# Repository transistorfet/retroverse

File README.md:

RetroVerse
==========

###### *Started August 06, 2023*

A collection of computer cards using the [VME bus](https://en.wikipedia.org/wiki/VMEbus) as a common
backplane, in the style of modular computer equipment, laboratory test equipment, and industrial
controls systems.  The project name is a combination of Retro-computers (newly designed and built
computers that are based on old CPUs and parts), and Versa (the V in VME, which stands for Versa
Module Eurocard).

I've always liked the VME bus for its adaptability.  It's an asynchronous bus with dynamic sizing,
so it can support both controllers and peripherals that require different signaling speeds and bus
widths to communicate, without requiring a specialized bus interface chip.  It supports multiple
controllers without the need for a special slot on the backplane, because it uses daisy chained
priority bus arbitration.  It's based on the Eurocard standard form factor, and uses standard and
readily available DIN41612 connectors, comes in a 3U variant, and it's possible to still buy
equipment that conforms to the standard, namely card cases and power supplies.  The 3U Eurocard
standard, which uses 160x100mm boards, is also fairly affordable for PCB printing, and it's possible
to make not-quite-standard 100x100mm cards, which can be printed for as low as $2.  The bus is
perhaps slow by modern standards, but for CPUs that are below 100MHz, it's the perfect bus to build
16-bit and 32-bit retro computers around.

So far, I have bought an off-the-shelf desktop card case from
[Schroff](https://schroff.nvent.com/en-de/products/enc24576-106) via Digikey (backordered), a used
Schroff 3U 11-slot backplane from eBay, and an affordable [MeanWell power
supply](https://www.meanwell.com/productPdf.aspx?i=488) to power it.  I've designed and built a CPU
card with a Motorola MC68030, onboard static RAM and Flash memory, and two serial ports, a small
16-bit memory card with up to 4MB of static RAM, and a board for handling the bus arbitration and
interrupt signals on the bus (separate from the CPU card since I intend to use multiple CPU cards in
the same system).  I've also built Tom Storey's CompactFlash card from
[COMET](https://github.com/tomstorey/COMET) to use as the main secondary storage for the system.
Before building these, I had also designed and built a generic card using an STM32 microcontroller
wired to the bus signals called
[BigBoy](https://github.com/transistorfet/retroverse/tree/main/components/bigboy), which I had hoped
to use as a bus analyzer, but it's a bit too slow for that, so I'll probably program it as a generic
peripheral instead.

I had originally intended to design and build my own backplane using 4-row connectors with some of
the P2 connector's signals on an extended P1, but I abandoned that idea in the interest of
interoperability with existing used VME equipment and ended up buying a used 11-slot Schroff
backplane from eBay.  Tom Storey has designed a 3-slot and 8-slot backplane as part of
[COMET](https://github.com/tomstorey/COMET) which is a good choice for those who wish to build their
own.

I also intend to eventually make an MC68010 version using only DIP chips and hopefully all hardwired
logic, so that there's no need for specialized PLD programmers.  I might also make cards with other
CPUs.  It should be possible for the system to support different CPUs in the same system at the same
time, running their own code.  My larger hope is for the VME bus to be used more broadly in the
hobbyist retro computer community as a common means of constructing systems.

Some of the design and build process was live-streamed and recordings are available at
[youtube.com/@transistorfet](https://www.youtube.com/@transistorfet)

Why VMEbus?
-----------

* it uses the eurocard form factor, and equipment such as cases can still be bought new or used

* it's asynchronous, so it can support devices operating at different speeds

* it supports dynamic bus sizing for 8-bit, 16-bit, and multiplexed 32-bit operations in 3U

* in the 6U form factor, it can also support full 32-bit or multiplexed 64-bit operations

* the DIN41612 connectors it uses are still widely available with solder tails

* supports cheap 3U board sizes of 100mm x 160mm or 100mm x 100mm

* also supports 6U board sizes for bigger and more complex devices

Why Not VMEBus?
---------------

* it can be a bit more complicated to interface to for simple 8-bit systems

* it's slower than newer buses like CompactPCI

* when using passive termination instead of active termination, it can draw a lot of current (2A+)
  with no cards

* each signal can draw a fair amount of current, which may be out of range for some logic chips (the
  standard requires that each pin can sink 48mA or more but typically it's <25mA in smaller and
  slower systems)

About VMEbus
------------

* [Understanding VMEBus](https://mdavidsaver.github.io/epics-doc/vme/understanding-vme.pdf)
* [VME FAQ from VITA](https://www.vita.com/VMEbus-FAQ)
* [VME P1 Connector Pinout](https://allpinouts.org/pinouts/connectors/buses/vme-versamodule-eurocard-p1/)
* [VME64](https://www.ge.infn.it/~musico/Vme/Vme64.pdf)
* [VMEBus on InterfaceBus.com](https://web.archive.org/web/20231220065144/http://www.interfacebus.com/Design_Connector_VME.html)

Other VME Projects
------------------

#### VMEbus prototyping card PCB:

* [https://github.com/rhaamo/VME](https://github.com/rhaamo/VME)

#### Proto Boards, Blanking Plates, Plate Adapters, ECB backplanes:

* [https://www.ebay.ca/usr/martenelectric](https://www.ebay.ca/usr/martenelectric)
* [https://www.martenelectric.cz/index.html](https://www.martenelectric.cz/index.html)

#### COMET backplane, prototyping card, and single board computer:

* [https://hackaday.io/project/192539-comet68k](https://hackaday.io/project/192539-comet68k)
* [https://github.com/tomstorey/COMET](https://github.com/tomstorey/COMET)
* computer card is missing bus arbitration, but the backplane supports it

[If you know of any other hobbyist VME components or projects that others can build, please get in
contact with me.  I'd love to add them to this list]

Single-CPU System
-----------------

This is generally where I'm at, as of March 2025.  I have a simple single-CPU system with
SystemBoard, k30p-VME, Tom Storey's CF Card, and MemBird Woodcock (although it's not used by the
software atm).  It can boot [Gloworm](https://github.com/transistorfet/gloworm), using the CF card
as the ATA device, and the FTDIs on k30p as the TTY and a SLIP connection for networking.  I can
ping it from my computer over SLIP, and run applications off the CF card.

![alt text](images/complete-single-cpu-system-front.jpg "A schroff 3U 63HP PropacPro case, looking face on and a bit downward at the front, which is trimmed in a very dark grey aluminum piece with two straight dull blue rounded aluminum top and bottom trim above and below where the cards are inserted.  The top of the case, which is barely showing, is light grey.  It has space for 15 slots spaced out horizontally, where cards can be inserted, oriented vertically, along bright red plastic guide rails.  Only 7 of the 10 guide rails are showing, with the others blocked by the front panels of 3 of the cards, with a gap of 3 slots between the second and third one.  The right 5 slots don't have guide rails.  The left-most slot has a blank aluminum plate with a few holes in it that allow a bright deep green LED inside to shine through.  Next to it is a white aluminum panel with black text that shows a partially obscured ComputieVME with a Motorola logo and k30p-VME below that.  It has 4 rows of pairs of LEDs and buttons, two USB-C ports with a mauve and a teal green cable plugged into each, and a white trapezoid handle below.  There's an empty slot and then Tom Storey's CF card is next to that with a CompactFlash card inserted in the front and no front panel.  Membird is next to it but not visible except for the dull green power LED.  BigBoy with a similar custom white aluminum front panel is next to it, with BigBoy in black text, 2 x 2 blue LEDs, a microSD slot, microB USB and RJ-11 jack labelled Ethernet on the front panel.  The right half of the 11-slot VME backplane is just visible, mounted in the left part of the case, with a space visible in the back where the remaining 4-slots-worth of space shows the back of the case, and the rear of the black power entry module.  Mounted in the right-most side of the case is a Meanwell powersupply taking up 8HP (2 slots), and the full 3U of height, wrapped in a thin metal shell with a diagonal pattern of round holes that expose most of the inside.  An 8HP blank plate with 4 knurled thumb-screws in the 4 corners and a trapezoid handle at the bottom and a protective film with 2 vertical blue lines still covering it, is mounted in the right most spot to block the power supply.")
![alt text](images/basic-single-cpu-system-angle.jpg "A green PCB backplane that says Schroff with white DIN41612 connectors, and 4 cards plugged into the first 4 of 11 slots.  The first and last are short 100mm long cards with the last being red and shown clearly while the first is black and is mostly obscured by the others.  The second card is purple with a white aluminum frontpanel that says 'ComputieVME', a Motorola logo, and 'k30p-VME' near the top in black text, with a trapezoid grey handle at the bottom, and two USB-C cables coming out of the frontpanel, the top one being a mauve and the the bottom being a light teal green.  The third card is green and has a compact flash card sticking out the top with no frontpanel.  The view is looking mostly down and to the left with the backplane flat on a black metal shelving unit about waist high, with the cards sticking upwards.  An oscilloscope can be be seen on the same shelf behind the backplane, and a small white fan is just out of view.")
![alt text](images/basic-single-cpu-system-side-angle.jpg "A green PCB backplane with white DIN41612 connectors, and 4 cards plugged into the first 4 of 11 slots.  The first and last are short 100mm long cards with the last being red and can mostly been seen while the first is black and is mostly obscured by the others.  The second card is purple with a white aluminum frontpanel with a trapezoid grey handle at the bottom, and two USB-C cables coming out of the frontpanel, the top one being a mauve and the the bottom being a light teal green.  The third card is green and has a compact flash card sticking out the top with no frontpanel.  The view is looking mostly sideways and a bit to the left, with backplane flat on a black metal shelving unit about waist high, with the cards sticking upwards.  An oscilloscope can be be seen on the same shelf behind the backplane, partially obscured by the cards.  A small white fan is just out of view, and a small teal desk lamp is in the foreground shining on the cards.")

Desktop Case
------------

I bought a brand new Schroff PropacPro 3U 63HP 266mm deep Unshielded Complete Desktop case.  I
initially requested a quote from Schroff, but unsurprisingly they sent me back a list of authorized
redistributors instead.  It turned out that Digikey did actually have the cases available for
backorder but the listing was uncategorized, so you had to search specifically for the part number
to find it.

* [https://schroff.nvent.com/en-ca/products/enc24576-006](https://schroff.nvent.com/en-ca/products/enc24576-006)
* [https://www.digikey.ca/en/products/detail/schroff/24576006/24659562](https://www.digikey.ca/en/products/detail/schroff/24576006/24659562)

I also bought a [Schurter Power Entry
Module](https://www.digikey.ca/en/products/detail/schurter-inc/4304-6091/2645678) and cut a hole in
the back aluminum panel to install it.  It's wired to the Meanwell RT-85B power supply, and power
from that is wired to the backplane.  I'd like to eventually add a current meter on the front,
mounted in an 8HP blanking plate I've bought, but I'm still waiting for parts to arrive.

![alt text](images/Schroff-case-and-backplane.jpg "A 3U 63HP desktop case with very dark grey front front and dull blue trim pieces made of rounded aluminum above and below the front card mounting rails, which have many small M2.5 screw holes horizontally, top and bottom, and are bright bare aluminum.  The left most 10-slots out of a maximum 15 have bright red card guides.  The case is empty of cards, but a Schroff 11-slot backplane is mounted in the rear of the case, most of the way back, and the rear panel is not in place.  The backplane is a green PCB with large white DIN41612 connectors that take up as much space as there is exposed green PCB.  The rest of the inside of the case is untreated bare aluminum.  A bundle of blue covered wire pair is just visible behind the case to the left, and a desk lamp and lego flowers are way in the background to the left, and a trans flag is barely visible to the right.")
![alt text](images/Schroff-case-and-backplane-rear.jpg "The rear of a 3U 63HP desktop case with no back panel looking inward, with a big green PCB with yellow silkscreen and yellow vertical through-hole resistor networks on the left and right sides, a white pin connector on the right most side, orange capacitors and metal screw terminals for power along the bottom edge, and the pins of the back sides of the DIN41612 sockets showing through.  It is covering most of the right side of the inside of the case, mounted on the rear rails inside the case.  The case is a light grey aluminum with vertical plastic rear feet/bumpers on the left and right sides.")
![alt text](images/Schroff-case-rear-panel-with-custom-switch.jpg "The rear of a 3U 63HP desktop case with no back panel looking inward, with a big green PCB with yellow silkscreen and yellow vertical through-hole resistor networks on the left and right sides, a white pin connector on the right most side, orange capacitors and metal screw terminals for power along the bottom edge, and the pins of the back sides of the DIN41612 sockets showing through.  It is covering most of the right side of the inside of the case, mounted on the rear rails inside the case.  The case is a light grey aluminum with vertical plastic rear feet/bumpers on the left and right sides.")

Backplane
---------

I bought a Schroff 23000-041 11-Slot backplane, used from eBay.  Luckily it has automatic
daisy-chaining, so when a slot doesn't have a card in it, the daisy-chained signals are shorted in
order to bypass that slot.  It also has active termination, which I have enabled with the jumpers,
so it takes only 10mA of 5V power without any cards connected.

k30p-VME
--------

A CPU card with a Motorola 68030 CPU, and an ATF1508AS CPLD for the control logic.  It has 2MB of
static RAM onboard, 512KB of Flash, a MC68681 dual serial port controller, with space for two
onboard FTDIs, and some push-button and LEDs that can be controlled by the serial controller.  The
CPLD can control the onboard transceivers to make a VME request from the CPU, based on the address
that the CPU is requesting.  I've tested it with 8-bit and 16-bit cycles, but I've designed it with
the transceivers that are required to make an A40/MD32 bus access, and hope to implement it soon
using BigBoy as the test peripheral.

While building the first revision, I found a number of issues.  The transceivers don't turn off when
the CPLD is being programmed, or when it's unprogrammed, and that means they write into each other,
and can damage each other.  I reworked in some pull-up resistors for the /OE signals to disable the
transceivers when the CPLD outputs are low or tri-stated.  I also originally had the FTDI powered by
the board, which meant it would disconnect from the computer every time the board was power cycled,
which was quite problematic when testing.  I tried to rework it so that it was powered by the USB
bus, but at first that didn't work.  After replacing the chip with an external FTDI, I tried
reworking it again and found that the USB-C cable only works in one orientation because I don't have
the main differential pair from each side of the USB-C connector jumped together.  The full errata
is here:
[k30p-VME-rev1-errata](https://github.com/transistorfet/retroverse/blob/main/components/computie-vme/hardware/k30p-VME/revisions/k30p-VME-rev1-errata.txt)

![alt text](images/k30p-VME-rev.1-reworked-assembled.jpg "The fully assembled and unplugged k30p-VME CPU Card, with purple solder mask, white silkscreen text, and a big greyish-white DIN41612 connector on the right side.  A big black plastic PGA chip in the centre reads MC68030RP33B.  There is some rework to the transceivers on the right, with some chip resistors and red 30AWG wire soldered in place, and some red 30AWG wire around the FTDIs on the left to power them from the USB bus.  A mauve-coloured USB-C cable is connected to the first USB port and a teal green USB-C cable is connected to the second USB port (bottom)")

, a fuse holder, and a plug for an IEC power cable.  It's laying flat on the desk and just in view is the rear section of the inside frame of the case with the top and bottom panels removed showing the shiny aluminum rails with black silkscreen text showing the number markings from 1 to 63 HP, two rows which count in opposite directions and can be read in the orientation of ascending numbers (ie. the bottom row is right way up and the top row is upside down but could be read the right way from 1-63 if if the rail was turned around)")

MemBird Woodcock
----------------

A memory card with up to 4MB of either Static RAM or Pseudo-static RAM powered by either 5V or 3.3V,
which can be selected by a soldered jumper and by using different chips (memory and transceiver
chips in particular).  It can only respond to A24 cycles, and only 8-bit or 16-bit accesses, but
that should serve well enough as common memory for when I have multiple CPU cards.  In future I will
make another MemBird board with an FPGA and SDRAM to allow for 128MB+ of memory, but until then,
this will suffice.

The building of this board went really smoothly.  Soldering went better than normal for SMT parts.
I was using ChipQuik NoClean Liquid flux, which worked well.  I only had one chip that was visibly
unconnected on closer inspection, and I didn't find any unintended bridges.  The board was behaving
strangely when I first tested it before I cleaned the flux off, but once I cleaned it and let it dry
overnight, it worked perfectly.

It's named after the American Woodcock, a small bird that moves along with a slow rhythmic walk,
since this card only has a small amount of memory, and will be slower to access, being only 16-bits.

SystemboardSMT
--------------

A system board with an ATF1508AS in the centre, and a clock, and that's about it.  It's primary
function is to handle the bus arbitration logic, but I can also use it as a dummy 8-bit peripheral
for testing.

I designed and built this board second, before the k30p and MemBird Woodcock, because it was simple
and would act as a test for the ATF1508, which I hadn't used before (other than in the devkit I
bought from Atmel).  The initial logic for the bus arbitration state machine turned out to be very
wrong, and that was causing problems for the k30p, which was hanging indefinitely.  I thought it was
the k30p's logic, but it turned out it wasn't receiving the bus grant from this card.

BigBoy
------

This was the first card I made and I intended to use it as a bus analyzer among other things, but
it's a bit too slow to catch most cycles, so I think I'll need an FPGA card instead for that
function, but it can work as a slow peripheral.  It has an STM32H743 microcontroller in a 208 pin
QFP package in the centre with the 5V tolerant I/O connected directly to the VME bus for the control
signals, and through transceivers for the data and address signals.  On the board is also a 100BaseT
ethernet interface, a full speed USB port (so 12Mbps I assume is the fastest), a microSD card slot
(where I accidentally put the footprint on backwards), and a few headers for external FTDIs, I2C,
and SPI devices.

It's called BigBoy because it has the big boy microcontroller in the largest QFP package available,
with a big 4-row DIN41612 connector which was an idea to add an extra row to P1 for the upper data
and address signals of a 32-bit system, which is optional (the 4-row connector can be plugged into a
3-row or 4-row backplane).  I've mostly abandoned this idea in favour of sticking to the standard,
and using the A40/MD32 cycle on a 3U system, or perhaps eventually making a 6U system and cards if I
want full-sized, higher speed, 32- or 64-bit systems in the future, all while maintaining
interoperability with existing used backplanes.  The logo is of [Bronson the
Cat](https://www.instagram.com/iambronsoncat/?hl=en) who is *such a big boy*

. It has a large grep DIN41612 connector on the right side, and a metal-shielded RJ-45 jack and some buttons and LEDs on the left.")

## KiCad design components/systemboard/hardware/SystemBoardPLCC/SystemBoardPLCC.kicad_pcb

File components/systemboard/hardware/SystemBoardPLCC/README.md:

SystemBoard
===========

Status: Never Built

Latest: Rev. 1

### About

A somewhat generic card with an ATF1508 programmable logic device, which is intended to act as the
system board of the VME bus, handling the resolution and granting of the bus during bus
arbitration, and interrupt acknowledging.  It has a clock and a reset button, which can be
programmed in the logic to reset all devices on the bus.

I have not actually built this version of the card, and instead built the SystemBoardSMT after
finding out that the PLCC version of the ATF1508AS was End-of-Life, and out of stock at Digikey
and Mouser.  It should work, but I'd recommend comparing the signals to the other version.  There
maybe be one or two signals that should be shuffled, depending on what's most important.

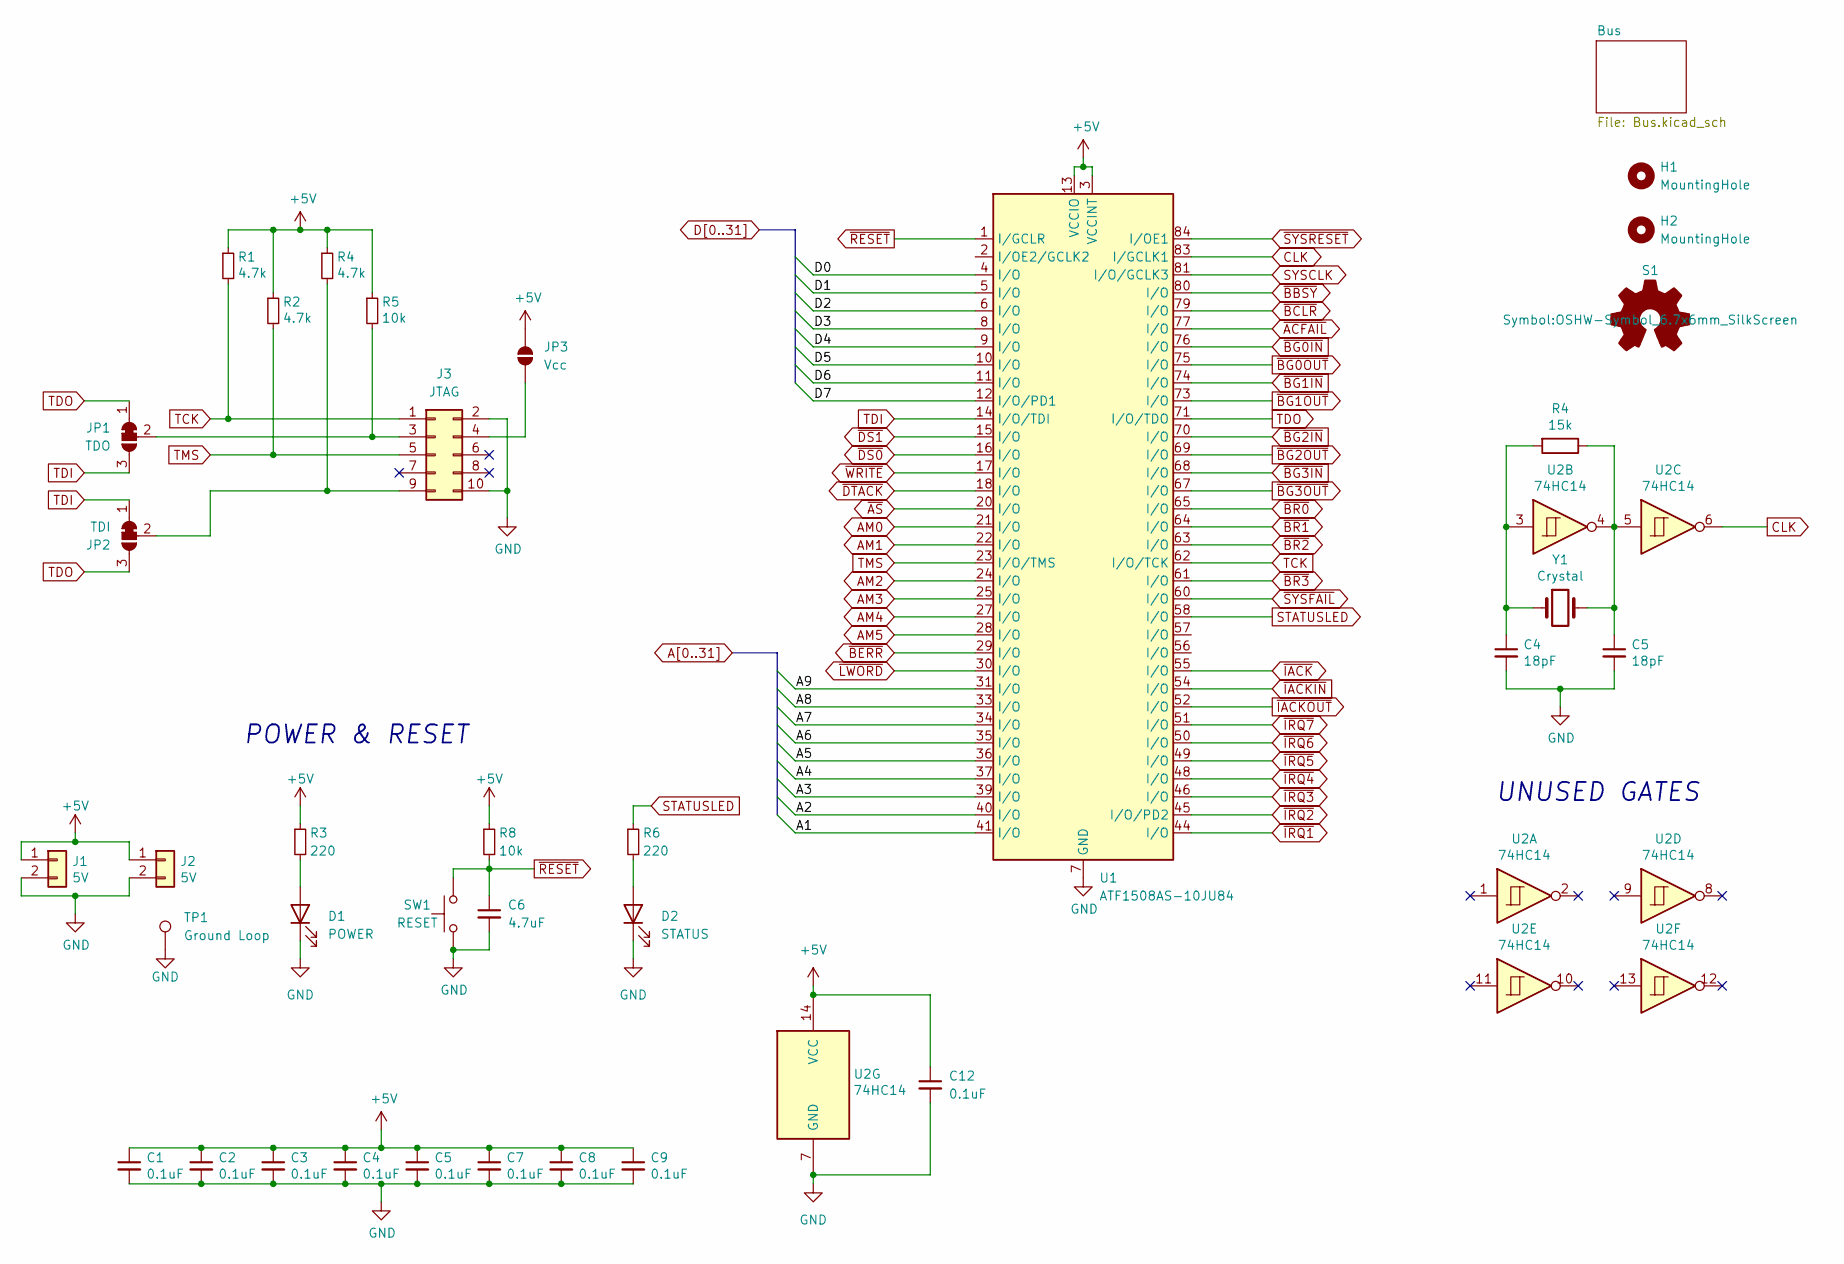
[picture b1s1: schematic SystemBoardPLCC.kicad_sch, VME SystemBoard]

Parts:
C1, C2, C3, C4, C7, C8, C9, C12: 0.1uF; C_0805_2012Metric_Pad1.18x1.45mm_HandSolder
C5: 18pF; C_Disc_D3.0mm_W2.0mm_P2.50mm
C6: 4.7uF; C_0805_2012Metric_Pad1.18x1.45mm_HandSolder
D1: POWER; LED_D3.0mm
D2: STATUS; LED_D3.0mm
H1, H2: MountingHole; MountingHole_2.7mm_M2.5_DIN965
J1, J2: 5V; PinHeader_1x02_P2.54mm_Vertical
J3: JTAG; PinHeader_2x05_P2.54mm_Vertical
JP1: TDO; SolderJumper-3_P1.3mm_Bridged12_RoundedPad1.0x1.5mm_NumberL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
JP2: TDI; SolderJumper-3_P1.3mm_Bridged12_RoundedPad1.0x1.5mm_NumberL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
JP3: Vcc; SolderJumper-2_P1.3mm_Open_RoundedPad1.0x1.5mm
R1, R2, R4: 4.7k; R_Axial_DIN0204_L3.6mm_D1.6mm_P5.08mm_Horizontal
R3, R6: 220; R_Axial_DIN0204_L3.6mm_D1.6mm_P5.08mm_Horizontal
R5, R8: 10k; R_Axial_DIN0204_L3.6mm_D1.6mm_P5.08mm_Horizontal
S1: Logo_Open_Hardware_Small; OSHW-Symbol_6.7x6mm_SilkScreen
SW1: RESET; SW_PUSH_6mm
TP1: Ground Loop; TestPoint_Loop_D2.60mm_Drill1.6mm_Beaded
U1: ATF1508AS-10JU84; PLCC-84_THT-Socket
U2: 74HC14; DIP-14_W7.62mm_LongPads
Y1: Crystal; Crystal_HC49-4H_Vertical

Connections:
A1: U1.41 (I/O); also elsewhere on the board
A2: U1.40 (I/O); also elsewhere on the board
A3: U1.39 (I/O); also elsewhere on the board
A4: U1.37 (I/O); also elsewhere on the board
A5: U1.36 (I/O); also elsewhere on the board
A6: U1.35 (I/O); also elsewhere on the board
A7: U1.34 (I/O); also elsewhere on the board
A8: U1.33 (I/O); also elsewhere on the board
A9: U1.31 (I/O); also elsewhere on the board
AM0: U1.21 (I/O); also elsewhere on the board
AM1: U1.22 (I/O); also elsewhere on the board
AM2: U1.24 (I/O); also elsewhere on the board
AM3: U1.25 (I/O); also elsewhere on the board
AM4: U1.27 (I/O); also elsewhere on the board
AM5: U1.28 (I/O); also elsewhere on the board
CLK: U1.83 (I/GCLK1), U2.6
D0: U1.4 (I/O); also elsewhere on the board
D1: U1.5 (I/O); also elsewhere on the board
D2: U1.6 (I/O); also elsewhere on the board
D3: U1.8 (I/O); also elsewhere on the board
D4: U1.9 (I/O); also elsewhere on the board
D5: U1.10 (I/O); also elsewhere on the board
D6: U1.11 (I/O); also elsewhere on the board
D7: U1.12 (I/O/PD1); also elsewhere on the board
GND: C1.2, C2.2, C3.2, C4.2, C5.2, C6.2, C7.2, C8.2, C9.2, C12.2, D1.1 (K), D2.1 (K), J1.2, J2.2, J3.2, J3.10, SW1.1, TP1.1, U1.7 (GND), U1.19 (GND), U1.32 (GND), U1.42 (GND), U1.47 (GND), U1.59 (GND), U1.72 (GND), U1.82 (GND), U2.7 (GND); also elsewhere on the board
unnamed: D1.2 (A), R3.2
unnamed: D2.2 (A), R6.2
unnamed: J3.3, JP1.2 (C), R5.2
unnamed: J3.4, JP3.1 (A)
STATUSLED: R6.1, U1.58 (I/O)
SYSCLK: U1.81 (I/O/GCLK3); also elsewhere on the board
TCK: J3.1, R1.2, U1.62 (I/O/TCK)
TDI: JP1.3 (B), JP2.1 (A), U1.14 (I/O/TDI)
TDO: JP1.1 (A), JP2.3 (B), U1.71 (I/O/TDO)
TMS: J3.5, R2.2, U1.23 (I/O/TMS)
~ACFAIL: U1.77 (I/O); also elsewhere on the board
~AS: U1.20 (I/O); also elsewhere on the board
~BBSY: U1.80 (I/O); also elsewhere on the board
~BCLR: U1.79 (I/O); also elsewhere on the board
~BERR: U1.29 (I/O); also elsewhere on the board
~BG0IN: U1.76 (I/O); also elsewhere on the board
~BG0OUT: U1.75 (I/O); also elsewhere on the board
~BG1IN: U1.74 (I/O); also elsewhere on the board
~BG1OUT: U1.73 (I/O); also elsewhere on the board
~BG2IN: U1.70 (I/O); also elsewhere on the board
~BG2OUT: U1.69 (I/O); also elsewhere on the board
~BG3IN: U1.68 (I/O); also elsewhere on the board
~BG3OUT: U1.67 (I/O); also elsewhere on the board
~BR0: U1.65 (I/O); also elsewhere on the board
~BR1: U1.64 (I/O); also elsewhere on the board
~BR2: U1.63 (I/O); also elsewhere on the board
~BR3: U1.61 (I/O); also elsewhere on the board
~DS0: U1.16 (I/O); also elsewhere on the board
~DS1: U1.15 (I/O); also elsewhere on the board
~DTACK: U1.18 (I/O); also elsewhere on the board
~IACKIN: U1.54 (I/O); also elsewhere on the board
~IACKOUT: U1.52 (I/O); also elsewhere on the board
~IACK: U1.55 (I/O); also elsewhere on the board
~IRQ1: U1.44 (I/O); also elsewhere on the board
~IRQ2: U1.45 (I/O/PD2); also elsewhere on the board
~IRQ3: U1.46 (I/O); also elsewhere on the board
~IRQ4: U1.48 (I/O); also elsewhere on the board
~IRQ5: U1.49 (I/O); also elsewhere on the board
~IRQ6: U1.50 (I/O); also elsewhere on the board
~IRQ7: U1.51 (I/O); also elsewhere on the board
~LWORD: U1.30 (I/O); also elsewhere on the board
~RESET: C6.1, R8.2, SW1.2, U1.1 (I/GCLR)
~SYSFAIL: U1.60 (I/O); also elsewhere on the board
~SYSRESET: U1.84 (I/OE1); also elsewhere on the board
~WRITE: U1.17 (I/O); also elsewhere on the board

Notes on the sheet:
POWER & RESET
UNUSED GATES

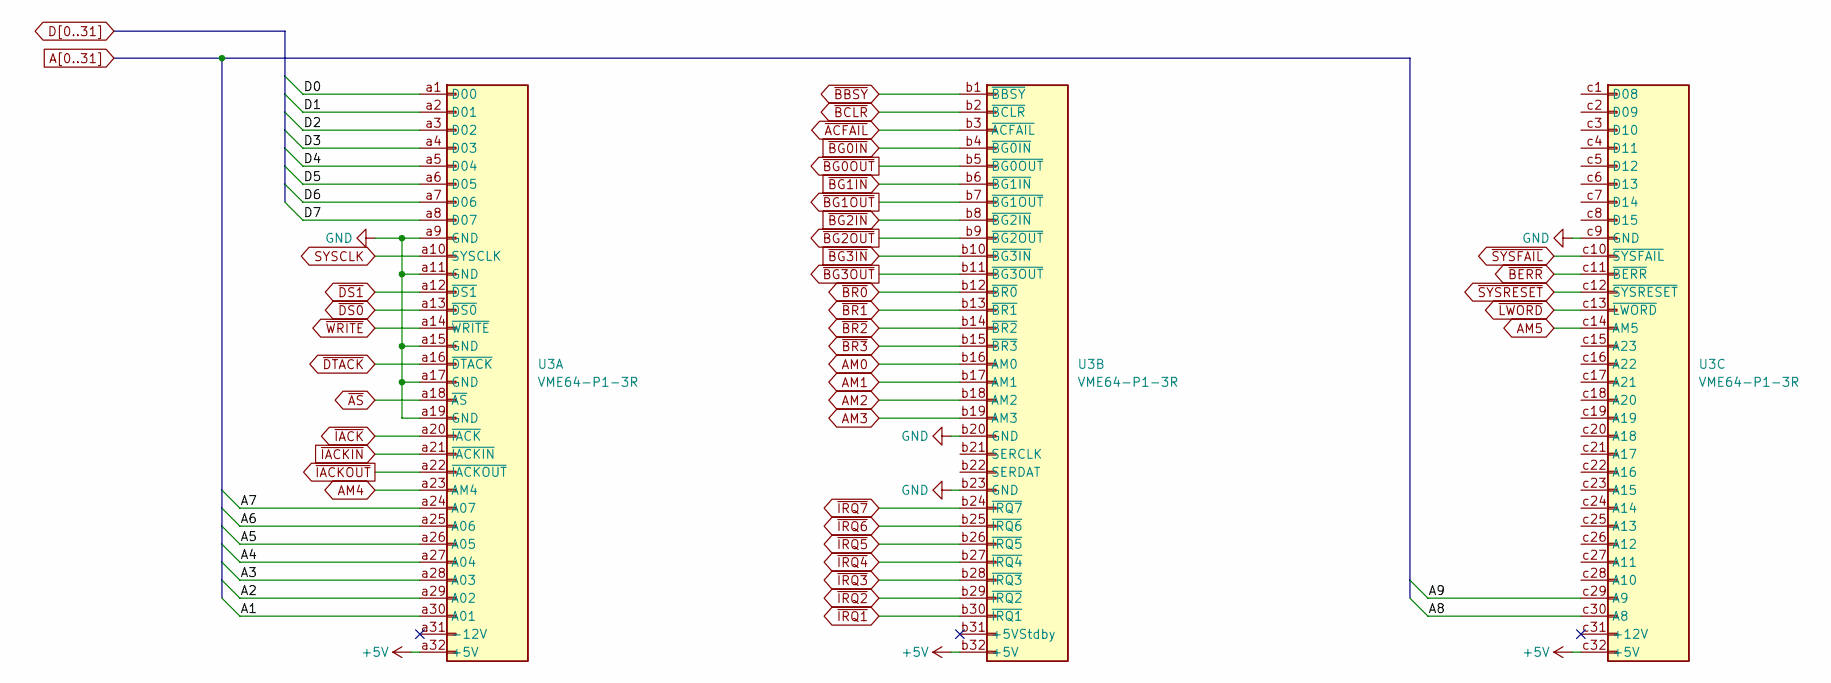
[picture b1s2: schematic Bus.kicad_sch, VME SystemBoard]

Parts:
U3: VME64-P1-3R; DIN41612_C_3x32_Male_Horizontal_THT

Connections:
A1: U3.a30 (A01); also elsewhere on the board
A2: U3.a29 (A02); also elsewhere on the board
A3: U3.a28 (A03); also elsewhere on the board
A4: U3.a27 (A04); also elsewhere on the board
A5: U3.a26 (A05); also elsewhere on the board
A6: U3.a25 (A06); also elsewhere on the board
A7: U3.a24 (A07); also elsewhere on the board
A8: U3.c30 (A8); also elsewhere on the board
A9: U3.c29 (A9); also elsewhere on the board
AM0: U3.b16 (AM0); also elsewhere on the board
AM1: U3.b17 (AM1); also elsewhere on the board
AM2: U3.b18 (AM2); also elsewhere on the board
AM3: U3.b19 (AM3); also elsewhere on the board
AM4: U3.a23 (AM4); also elsewhere on the board
AM5: U3.c14 (AM5); also elsewhere on the board
D0: U3.a1 (D00); also elsewhere on the board
D1: U3.a2 (D01); also elsewhere on the board
D2: U3.a3 (D02); also elsewhere on the board
D3: U3.a4 (D03); also elsewhere on the board
D4: U3.a5 (D04); also elsewhere on the board
D5: U3.a6 (D05); also elsewhere on the board
D6: U3.a7 (D06); also elsewhere on the board
D7: U3.a8 (D07); also elsewhere on the board
GND: U3.a9 (GND), U3.a11 (GND), U3.a15 (GND), U3.a17 (GND), U3.a19 (GND), U3.b20 (GND), U3.b23 (GND), U3.c9 (GND); also elsewhere on the board
SYSCLK: U3.a10 (SYSCLK); also elsewhere on the board
~ACFAIL: U3.b3 (~ACFAIL); also elsewhere on the board
~AS: U3.a18 (~AS); also elsewhere on the board
~BBSY: U3.b1 (~BBSY); also elsewhere on the board
~BCLR: U3.b2 (~BCLR); also elsewhere on the board
~BERR: U3.c11 (~BERR); also elsewhere on the board
~BG0IN: U3.b4 (~BG0IN); also elsewhere on the board
~BG0OUT: U3.b5 (~BG0OUT); also elsewhere on the board
~BG1IN: U3.b6 (~BG1IN); also elsewhere on the board
~BG1OUT: U3.b7 (~BG1OUT); also elsewhere on the board
~BG2IN: U3.b8 (~BG2IN); also elsewhere on the board
~BG2OUT: U3.b9 (~BG2OUT); also elsewhere on the board
~BG3IN: U3.b10 (~BG3IN); also elsewhere on the board
~BG3OUT: U3.b11 (~BG3OUT); also elsewhere on the board
~BR0: U3.b12 (~BR0); also elsewhere on the board
~BR1: U3.b13 (~BR1); also elsewhere on the board
~BR2: U3.b14 (~BR2); also elsewhere on the board
~BR3: U3.b15 (~BR3); also elsewhere on the board
~DS0: U3.a13 (~DS0); also elsewhere on the board
~DS1: U3.a12 (~DS1); also elsewhere on the board
~DTACK: U3.a16 (~DTACK); also elsewhere on the board
~IACKIN: U3.a21 (~IACKIN); also elsewhere on the board
~IACKOUT: U3.a22 (~IACKOUT); also elsewhere on the board
~IACK: U3.a20 (~IACK); also elsewhere on the board
~IRQ1: U3.b30 (~IRQ1); also elsewhere on the board
~IRQ2: U3.b29 (~IRQ2); also elsewhere on the board
~IRQ3: U3.b28 (~IRQ3); also elsewhere on the board
~IRQ4: U3.b27 (~IRQ4); also elsewhere on the board
~IRQ5: U3.b26 (~IRQ5); also elsewhere on the board
~IRQ6: U3.b25 (~IRQ6); also elsewhere on the board
~IRQ7: U3.b24 (~IRQ7); also elsewhere on the board
~LWORD: U3.c13 (~LWORD); also elsewhere on the board
~SYSFAIL: U3.c10 (~SYSFAIL); also elsewhere on the board
~SYSRESET: U3.c12 (~SYSRESET); also elsewhere on the board
~WRITE: U3.a14 (~WRITE); also elsewhere on the board

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
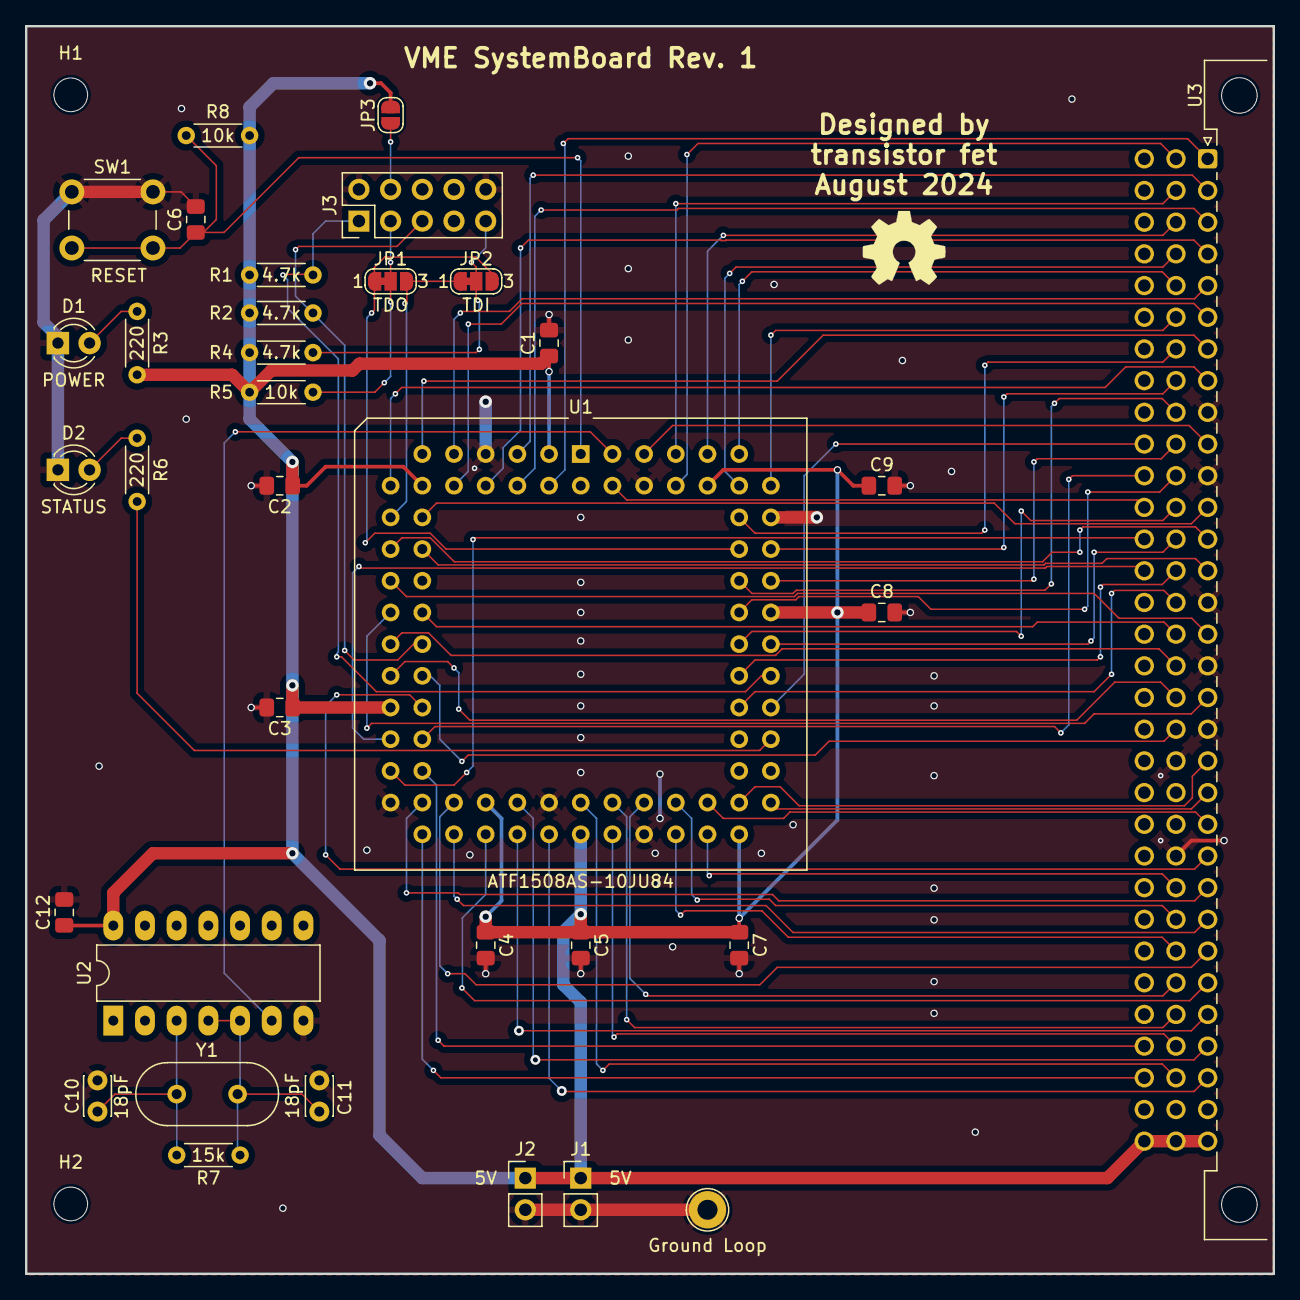
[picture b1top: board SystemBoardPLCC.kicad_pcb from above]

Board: 2 copper layers, 100.0 x 100.0 mm, 37 parts (0 on the bottom side), 74 nets.

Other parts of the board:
C10, C11: 18pF; C_Disc_D3.0mm_W2.0mm_P2.50mm
R7: 15k; R_Axial_DIN0204_L3.6mm_D1.6mm_P5.08mm_Horizontal

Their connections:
GND: C10.2, C11.2; also elsewhere on the board

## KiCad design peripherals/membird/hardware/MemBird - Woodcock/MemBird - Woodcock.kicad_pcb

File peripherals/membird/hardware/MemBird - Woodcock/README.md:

MemBird - Woodcock
==================

Status: Design but not yet built

Latest: Rev. 1

### About

A 16-bit VME memory card with 4MB of Static RAM at either 5V or 3.3V

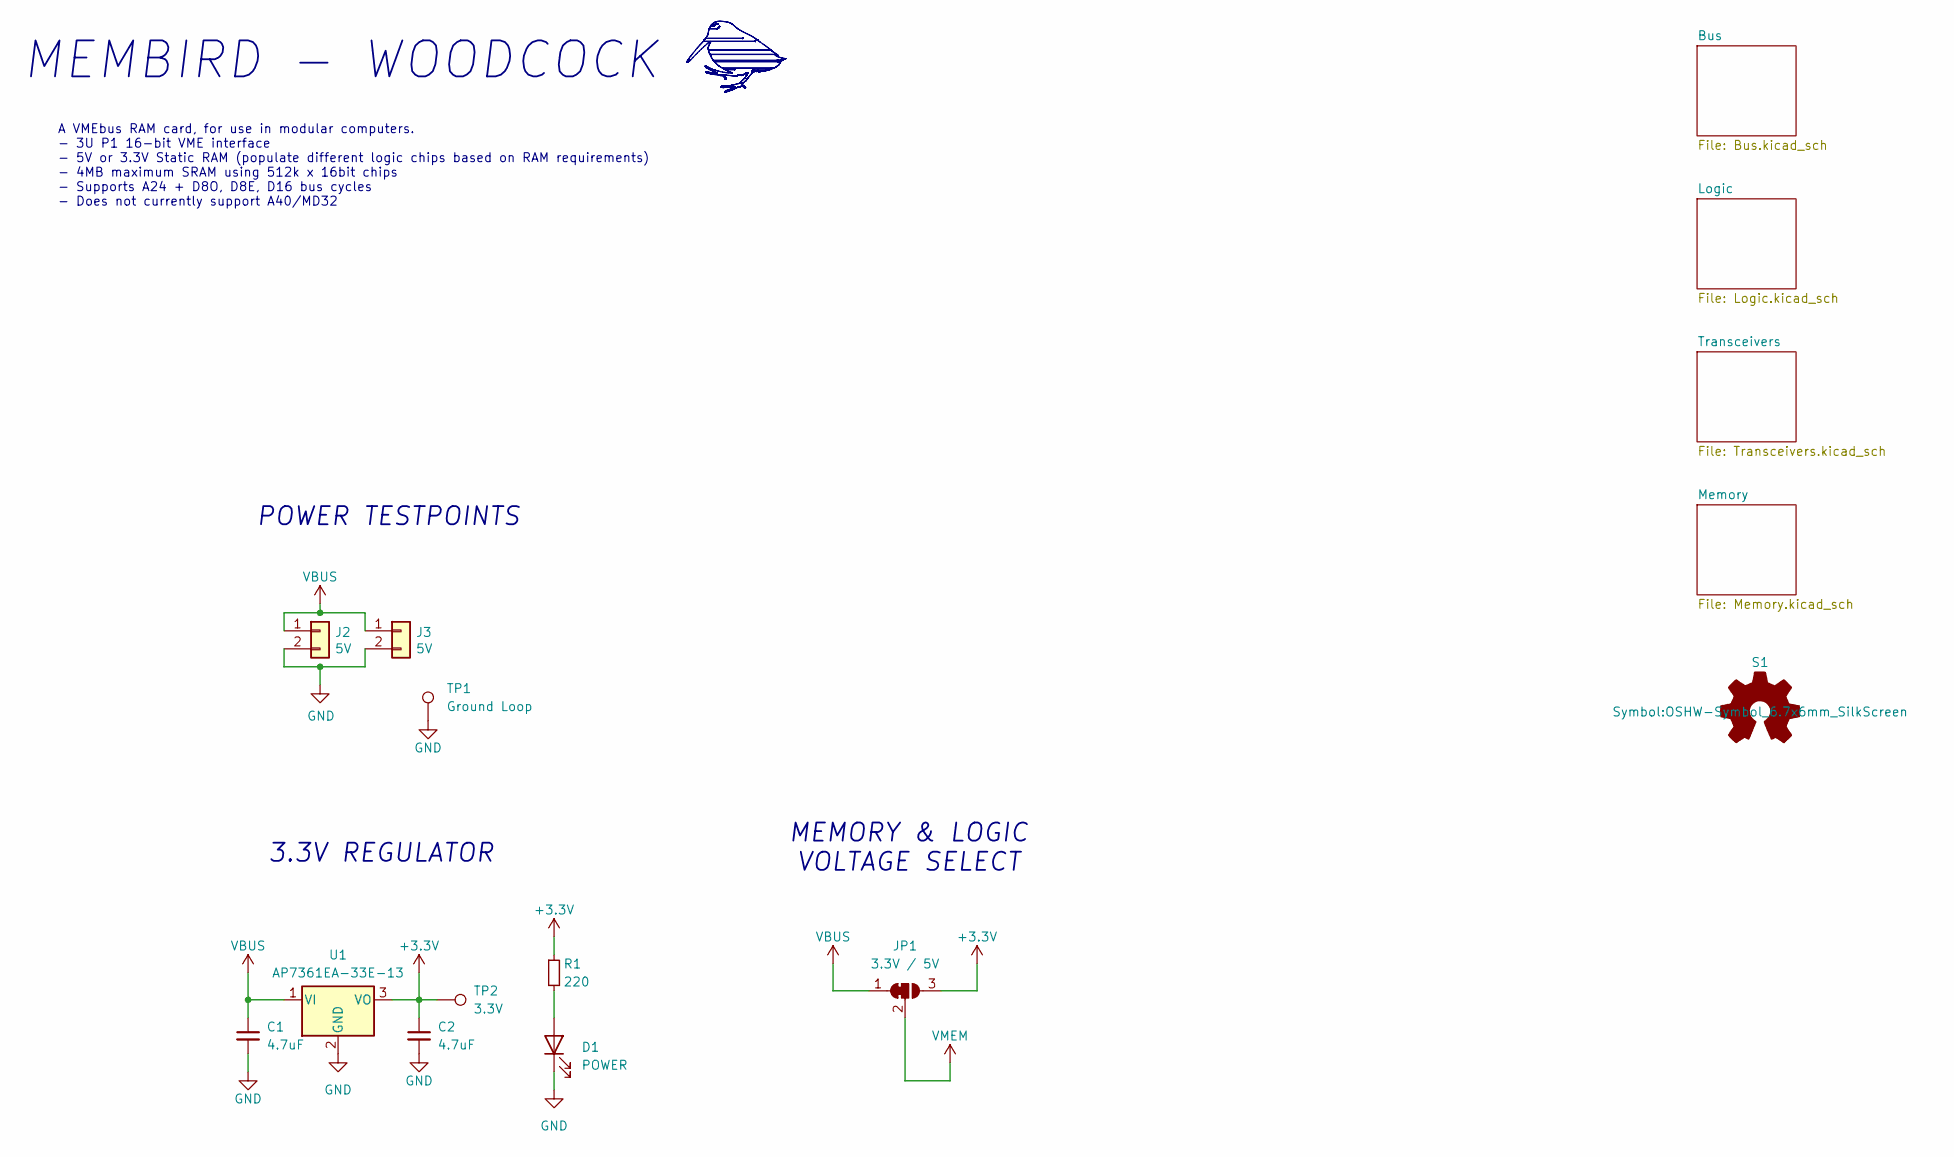
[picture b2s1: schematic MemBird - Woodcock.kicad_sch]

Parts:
C1, C2: 4.7uF; C_1206_3216Metric_Pad1.33x1.80mm_HandSolder
D1: POWER; LED_PLCC-2_3.4x3.0mm_KA
J2, J3: 5V; PinHeader_1x02_P2.54mm_Vertical
JP1: 3.3V / 5V; SolderJumper-3_P1.3mm_Bridged12_RoundedPad1.0x1.5mm_NumberL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
R1: 220; R_0805_2012Metric_Pad1.20x1.40mm_HandSolder
S1: Logo_Open_Hardware_Small; OSHW-Symbol_6.7x6mm_SilkScreen
TP1: Ground Loop; TestPoint_Loop_D2.60mm_Drill1.6mm_Beaded
TP2: 3.3V; TestPoint_THTPad_2.0x2.0mm_Drill1.0mm
U1: AP7361EA-33E-13; SOT-223

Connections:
+3.3V: C2.1, JP1.3 (B), R1.1, TP2.1, U1.3 (VO)
GND: C1.2, C2.2, D1.1 (K), J2.2, J3.2, TP1.1, U1.2 (GND); also elsewhere on the board
unnamed: D1.2 (A), R1.2
VBUS: C1.1, J2.1, J3.1, JP1.1 (A), U1.1 (VI); also elsewhere on the board
VMEM: JP1.2 (C); also elsewhere on the board

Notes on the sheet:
MEMBIRD - WOODCOCK
A VMEbus RAM card, for use in modular computers. - 3U P1 16-bit VME interface - 5V or 3.3V Static RAM (populate different logic chips based on RAM requirements) - 4MB maximum SRAM using 512k x 16bit chips - Supports A24 + D8O, D8E, D16 bus cycles - Does not currently support A40/MD32
3.3V REGULATOR
POWER TESTPOINTS
MEMORY & LOGIC VOLTAGE SELECT

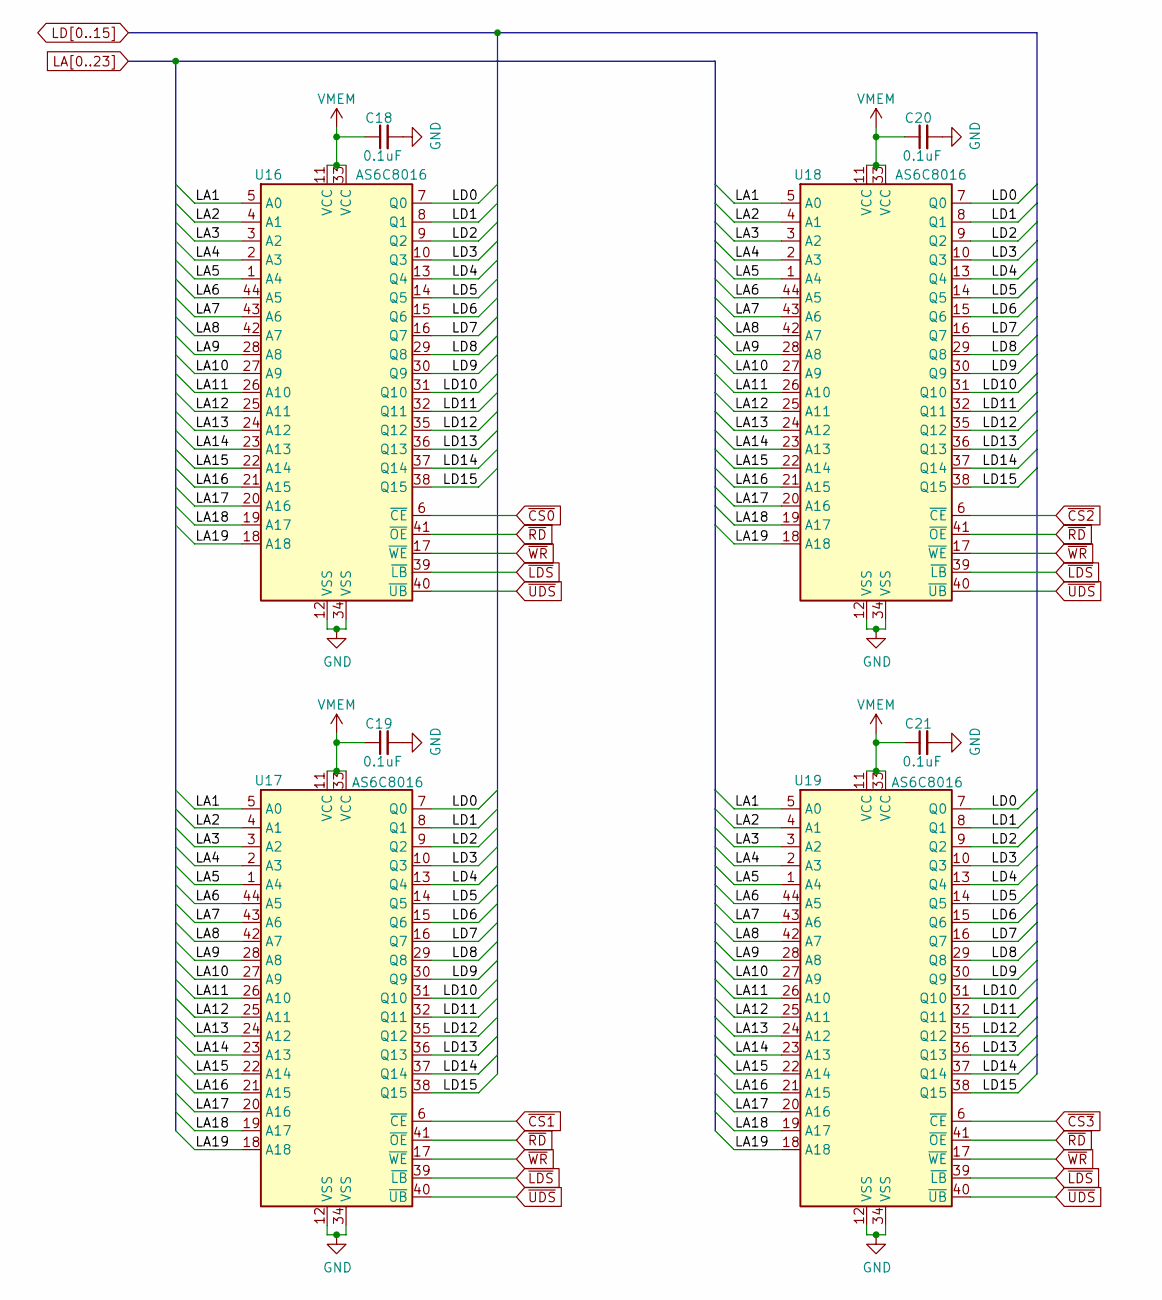
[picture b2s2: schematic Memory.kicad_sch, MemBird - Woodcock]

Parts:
C18, C19, C20, C21: 0.1uF; C_0805_2012Metric_Pad1.18x1.45mm_HandSolder
U16, U17, U18, U19: AS6C8016; TSOP-II-44_10.16x18.41mm_P0.8mm

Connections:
GND: C18.2, C19.2, C20.2, C21.2, U16.12 (VSS), U16.34 (VSS), U17.12 (VSS), U17.34 (VSS), U18.12 (VSS), U18.34 (VSS), U19.12 (VSS), U19.34 (VSS); also elsewhere on the board
LA1: U16.5 (A0), U17.5 (A0), U18.5 (A0), U19.5 (A0); also elsewhere on the board
LA2: U16.4 (A1), U17.4 (A1), U18.4 (A1), U19.4 (A1); also elsewhere on the board
LA3: U16.3 (A2), U17.3 (A2), U18.3 (A2), U19.3 (A2); also elsewhere on the board
LA4: U16.2 (A3), U17.2 (A3), U18.2 (A3), U19.2 (A3); also elsewhere on the board
LA5: U16.1 (A4), U17.1 (A4), U18.1 (A4), U19.1 (A4); also elsewhere on the board
LA6: U16.44 (A5), U17.44 (A5), U18.44 (A5), U19.44 (A5); also elsewhere on the board
LA7: U16.43 (A6), U17.43 (A6), U18.43 (A6), U19.43 (A6); also elsewhere on the board
LA8: U16.42 (A7), U17.42 (A7), U18.42 (A7), U19.42 (A7); also elsewhere on the board
LA9: U16.28 (A8), U17.28 (A8), U18.28 (A8), U19.28 (A8); also elsewhere on the board
LA10: U16.27 (A9), U17.27 (A9), U18.27 (A9), U19.27 (A9); also elsewhere on the board
LA11: U16.26 (A10), U17.26 (A10), U18.26 (A10), U19.26 (A10); also elsewhere on the board
LA12: U16.25 (A11), U17.25 (A11), U18.25 (A11), U19.25 (A11); also elsewhere on the board
LA13: U16.24 (A12), U17.24 (A12), U18.24 (A12), U19.24 (A12); also elsewhere on the board
LA14: U16.23 (A13), U17.23 (A13), U18.23 (A13), U19.23 (A13); also elsewhere on the board
LA15: U16.22 (A14), U17.22 (A14), U18.22 (A14), U19.22 (A14); also elsewhere on the board
LA16: U16.21 (A15), U17.21 (A15), U18.21 (A15), U19.21 (A15); also elsewhere on the board
LA17: U16.20 (A16), U17.20 (A16), U18.20 (A16), U19.20 (A16); also elsewhere on the board
LA18: U16.19 (A17), U17.19 (A17), U18.19 (A17), U19.19 (A17); also elsewhere on the board
LA19: U16.18 (A18), U17.18 (A18), U18.18 (A18), U19.18 (A18); also elsewhere on the board
LD0: U16.7 (Q0), U17.7 (Q0), U18.7 (Q0), U19.7 (Q0); also elsewhere on the board
LD1: U16.8 (Q1), U17.8 (Q1), U18.8 (Q1), U19.8 (Q1); also elsewhere on the board
LD2: U16.9 (Q2), U17.9 (Q2), U18.9 (Q2), U19.9 (Q2); also elsewhere on the board
LD3: U16.10 (Q3), U17.10 (Q3), U18.10 (Q3), U19.10 (Q3); also elsewhere on the board
LD4: U16.13 (Q4), U17.13 (Q4), U18.13 (Q4), U19.13 (Q4); also elsewhere on the board
LD5: U16.14 (Q5), U17.14 (Q5), U18.14 (Q5), U19.14 (Q5); also elsewhere on the board
LD6: U16.15 (Q6), U17.15 (Q6), U18.15 (Q6), U19.15 (Q6); also elsewhere on the board
LD7: U16.16 (Q7), U17.16 (Q7), U18.16 (Q7), U19.16 (Q7); also elsewhere on the board
LD8: U16.29 (Q8), U17.29 (Q8), U18.29 (Q8), U19.29 (Q8); also elsewhere on the board
LD9: U16.30 (Q9), U17.30 (Q9), U18.30 (Q9), U19.30 (Q9); also elsewhere on the board
LD10: U16.31 (Q10), U17.31 (Q10), U18.31 (Q10), U19.31 (Q10); also elsewhere on the board
LD11: U16.32 (Q11), U17.32 (Q11), U18.32 (Q11), U19.32 (Q11); also elsewhere on the board
LD12: U16.35 (Q12), U17.35 (Q12), U18.35 (Q12), U19.35 (Q12); also elsewhere on the board
LD13: U16.36 (Q13), U17.36 (Q13), U18.36 (Q13), U19.36 (Q13); also elsewhere on the board
LD14: U16.37 (Q14), U17.37 (Q14), U18.37 (Q14), U19.37 (Q14); also elsewhere on the board
LD15: U16.38 (Q15), U17.38 (Q15), U18.38 (Q15), U19.38 (Q15); also elsewhere on the board
VMEM: C18.1, C19.1, C20.1, C21.1, U16.11 (VCC), U16.33 (VCC), U17.11 (VCC), U17.33 (VCC), U18.11 (VCC), U18.33 (VCC), U19.11 (VCC), U19.33 (VCC); also elsewhere on the board
~CS0: U16.6 (~CE); also elsewhere on the board
~CS1: U17.6 (~CE); also elsewhere on the board
~CS2: U18.6 (~CE); also elsewhere on the board
~CS3: U19.6 (~CE); also elsewhere on the board
~LDS: U16.39 (~LB), U17.39 (~LB), U18.39 (~LB), U19.39 (~LB); also elsewhere on the board
~RD: U16.41 (~OE), U17.41 (~OE), U18.41 (~OE), U19.41 (~OE); also elsewhere on the board
~UDS: U16.40 (~UB), U17.40 (~UB), U18.40 (~UB), U19.40 (~UB); also elsewhere on the board
~WR: U16.17 (~WE), U17.17 (~WE), U18.17 (~WE), U19.17 (~WE); also elsewhere on the board
